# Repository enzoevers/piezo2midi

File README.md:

# piezo2midi

This project contains the hardware and software to read piezo inputs and convert them to a midi signal.

The main usecase is electronic drums. But it should be generic enough to be use by any piezo input.

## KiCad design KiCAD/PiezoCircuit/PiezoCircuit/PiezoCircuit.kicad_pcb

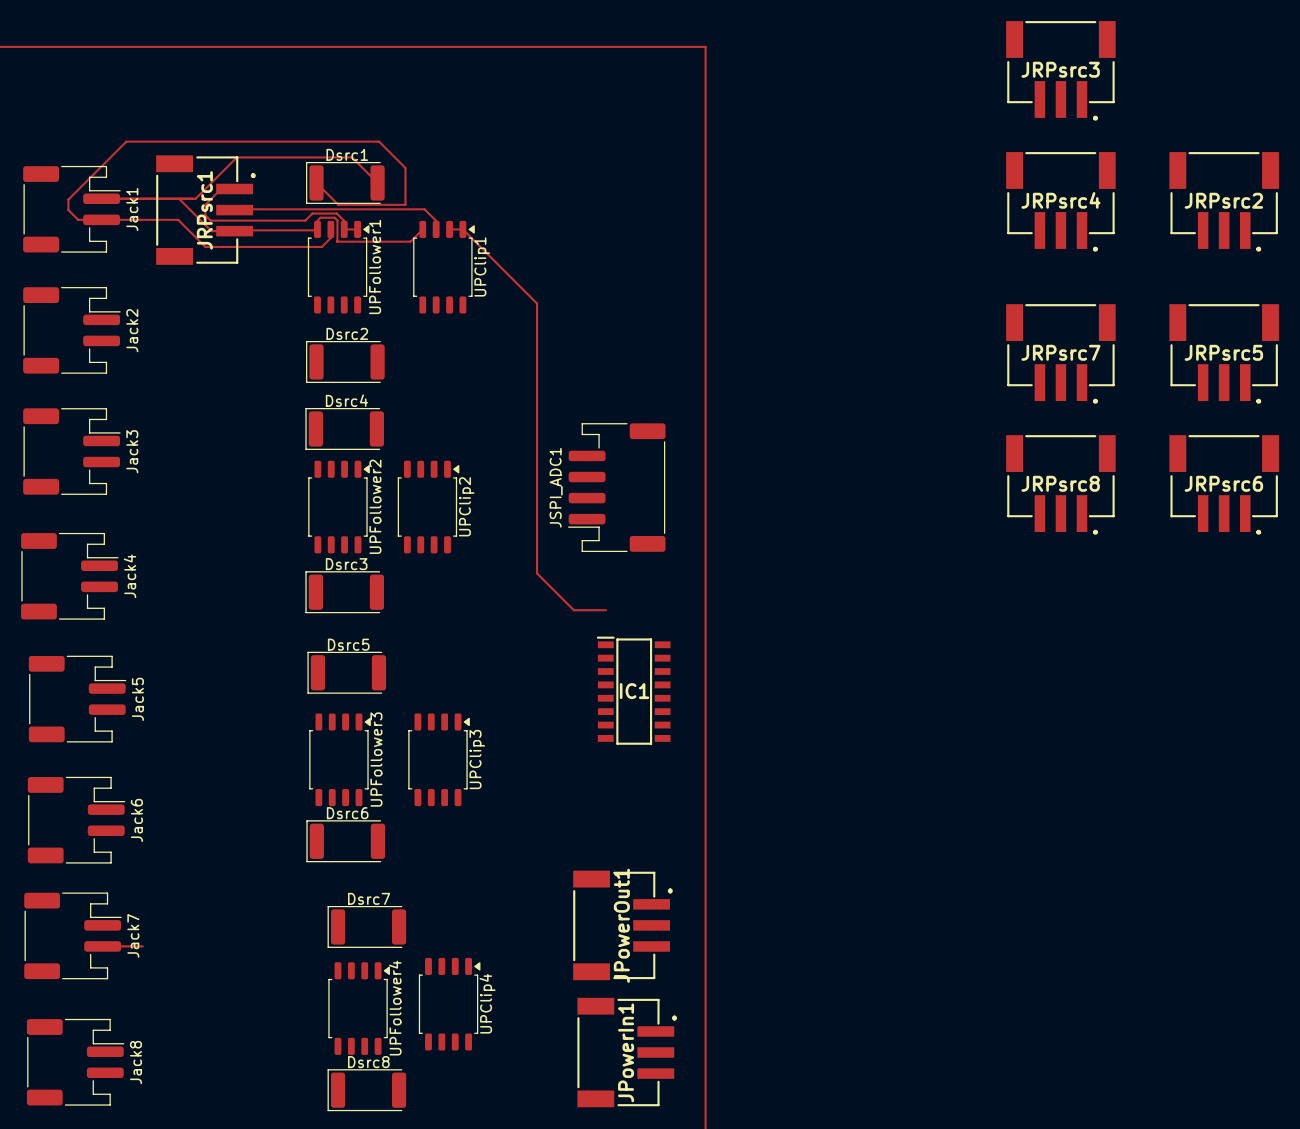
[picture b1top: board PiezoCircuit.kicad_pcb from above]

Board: 2 copper layers, 36 parts (0 on the bottom side), 40 nets.

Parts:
Dsrc1, Dsrc2, Dsrc3, Dsrc4, Dsrc5, Dsrc6, Dsrc7, Dsrc8: D_2512_6332Metric
IC1: MCP3008-I_SL; SOIC127P600X175-16N
JPowerIn1: S3B-PH-SM4-TB_LF__SN_; S3BPHSM4TBLFSN
JPowerOut1: S3B-PH-SM4-TB_LF__SN_; S3BPHSM4TBLFSN
JRPsrc1, JRPsrc2, JRPsrc3, JRPsrc4, JRPsrc5, JRPsrc6, JRPsrc7, JRPsrc8: S3B-PH-SM4-TB_LF__SN_; S3BPHSM4TBLFSN
JSPI_ADC1: Conn_01x04; JST_PH_S4B-PH-SM4-TB_1x04-1MP_P2.00mm_Horizontal
Jack1, Jack2, Jack3, Jack4, Jack5, Jack6, Jack7, Jack8: Conn_01x02; JST_PH_S2B-PH-SM4-TB_1x02-1MP_P2.00mm_Horizontal
UPClip1, UPClip2, UPClip3, UPClip4: LM358; SOIC-8_5.3x5.3mm_P1.27mm
UPFollower1, UPFollower2, UPFollower3, UPFollower4: LM358; SOIC-8_5.3x5.3mm_P1.27mm

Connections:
+5V: IC1.15 (VREF), IC1.16 (VDD)
/SPI_CLK_ADC: IC1.13 (CLK), JSPI_ADC1.4
/SPI_MISO_ADC: IC1.12 (DOUT), JSPI_ADC1.3
/SPI_MOSI_ADC: IC1.11 (DIN), JSPI_ADC1.2
/ScaledInput0: IC1.1 (CH0), UPClip1.1, UPClip1.2 (-)
/ScaledInput1: IC1.2 (CH1), UPClip1.6 (-), UPClip1.7
/ScaledInput2: IC1.3 (CH2), UPClip2.1, UPClip2.2 (-)
/ScaledInput3: IC1.4 (CH3), UPClip2.6 (-), UPClip2.7
/ScaledInput4: IC1.5 (CH4), UPClip3.1, UPClip3.2 (-)
/ScaledInput5: IC1.6 (CH5), UPClip3.6 (-), UPClip3.7
/ScaledInput6: IC1.7 (CH6), UPClip4.1, UPClip4.2 (-)
/ScaledInput7: IC1.8 (CH7), UPClip4.6 (-), UPClip4.7
/VMCUref: JPowerIn1.3, JPowerOut1.3
/VPiezoRef: JPowerIn1.1, JPowerOut1.1
/src_tip_0: Dsrc1.1 (K), Jack1.2, UPFollower1.3 (+)
/src_tip_1: Dsrc2.1 (K), Jack2.2, UPFollower1.5 (+)
/src_tip_2: Dsrc3.1 (K), Jack3.2, UPFollower2.3 (+)
/src_tip_3: Dsrc4.1 (K), Jack4.2, UPFollower2.5 (+)
/src_tip_4: Dsrc5.1 (K), Jack5.2, UPFollower3.3 (+)
/src_tip_5: Dsrc6.1 (K), Jack6.2, UPFollower3.5 (+)
/src_tip_6: Dsrc7.1 (K), Jack7.2, UPFollower4.3 (+)
/src_tip_7: Dsrc8.1 (K), Jack8.2, UPFollower4.5 (+)
/~SPI_CS_ADC: IC1.10 (~CS/SHDN), JSPI_ADC1.1
GND: Dsrc1.2 (A), Dsrc2.2 (A), Dsrc3.2 (A), Dsrc4.2 (A), Dsrc5.2 (A), Dsrc6.2 (A), Dsrc7.2 (A), Dsrc8.2 (A), IC1.9 (DGND), IC1.14 (AGND), JPowerIn1.2, JPowerOut1.2, JRPsrc1.3, JRPsrc2.3, JRPsrc3.3, JRPsrc4.3, JRPsrc5.3, JRPsrc6.3, JRPsrc7.3, JRPsrc8.3, Jack1.1, Jack2.1, Jack3.1, Jack4.1, Jack5.1, Jack6.1, Jack7.1, Jack8.1, UPClip1.4 (V-), UPClip2.4 (V-), UPClip3.4 (V-), UPClip4.4 (V-), UPFollower1.4 (V-), UPFollower2.4 (V-), UPFollower3.4 (V-), UPFollower4.4 (V-)
unnamed: JRPsrc1.2, UPClip1.3 (+)
unnamed: JRPsrc2.2, UPClip1.5 (+)
unnamed: JRPsrc3.2, UPClip2.3 (+)
unnamed: JRPsrc4.2, UPClip2.5 (+)
unnamed: JRPsrc5.2, UPClip3.3 (+)
unnamed: JRPsrc6.2, UPClip3.5 (+)
unnamed: JRPsrc7.2, UPClip4.3 (+)
unnamed: JRPsrc8.2, UPClip4.5 (+)
unnamed: JRPsrc1.1, UPFollower1.1, UPFollower1.2 (-)
unnamed: JRPsrc2.1, UPFollower1.6 (-), UPFollower1.7
unnamed: JRPsrc3.1, UPFollower2.1, UPFollower2.2 (-)
unnamed: JRPsrc4.1, UPFollower2.6 (-), UPFollower2.7
unnamed: JRPsrc5.1, UPFollower3.1, UPFollower3.2 (-)
unnamed: JRPsrc6.1, UPFollower3.6 (-), UPFollower3.7
unnamed: JRPsrc7.1, UPFollower4.1, UPFollower4.2 (-)
unnamed: JRPsrc8.1, UPFollower4.6 (-), UPFollower4.7

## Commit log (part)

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2025-11-02 Describe project components
2025-11-14 Describe piezo circuit
2025-11-17 Describe the software design
2025-11-30 Describe the software requirements and high-level flow of the code
2025-11-30 Cleaning up the documentation
2025-12-13 Create high-level algorithm design
2025-12-24 Update piezo input circuit
2026-04-02 Setup the software structure for cross-platform development and testing. Additionally, implement basic DigitalIO and UART implementations for AVR microcontrollers.
2026-04-02 Run the pipeline on main as well
2026-04-04 Implement SPI for AVR and mocks
2026-04-04 Update SPI to only change the mentioned slave select line. Add DeselectSlave(...)
2026-04-04 Add image of Arduino uno pinout
2026-04-04 Implement MCP3008
2026-04-06 Implement MIDI
2026-04-06 Create a single function for the UART tests to create the ON_CALLS for ReadDefine
2026-06-13 Add code for delays
2026-06-14 Create script to get insight into the program size
2026-06-14 Use only python scripts
2026-06-15 Update avr toolchain script to also support linux and create linux docker image for building the project.
2026-06-18 Create analog channel logic
2026-06-19 Channel mapping
